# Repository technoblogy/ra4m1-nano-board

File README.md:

# RA4M1 Nano board
An Arduino Nano-sized board based on the Renesas RA4M1 ARM processor.

For more information see <http://www.technoblogy.com/show?4JVF>.

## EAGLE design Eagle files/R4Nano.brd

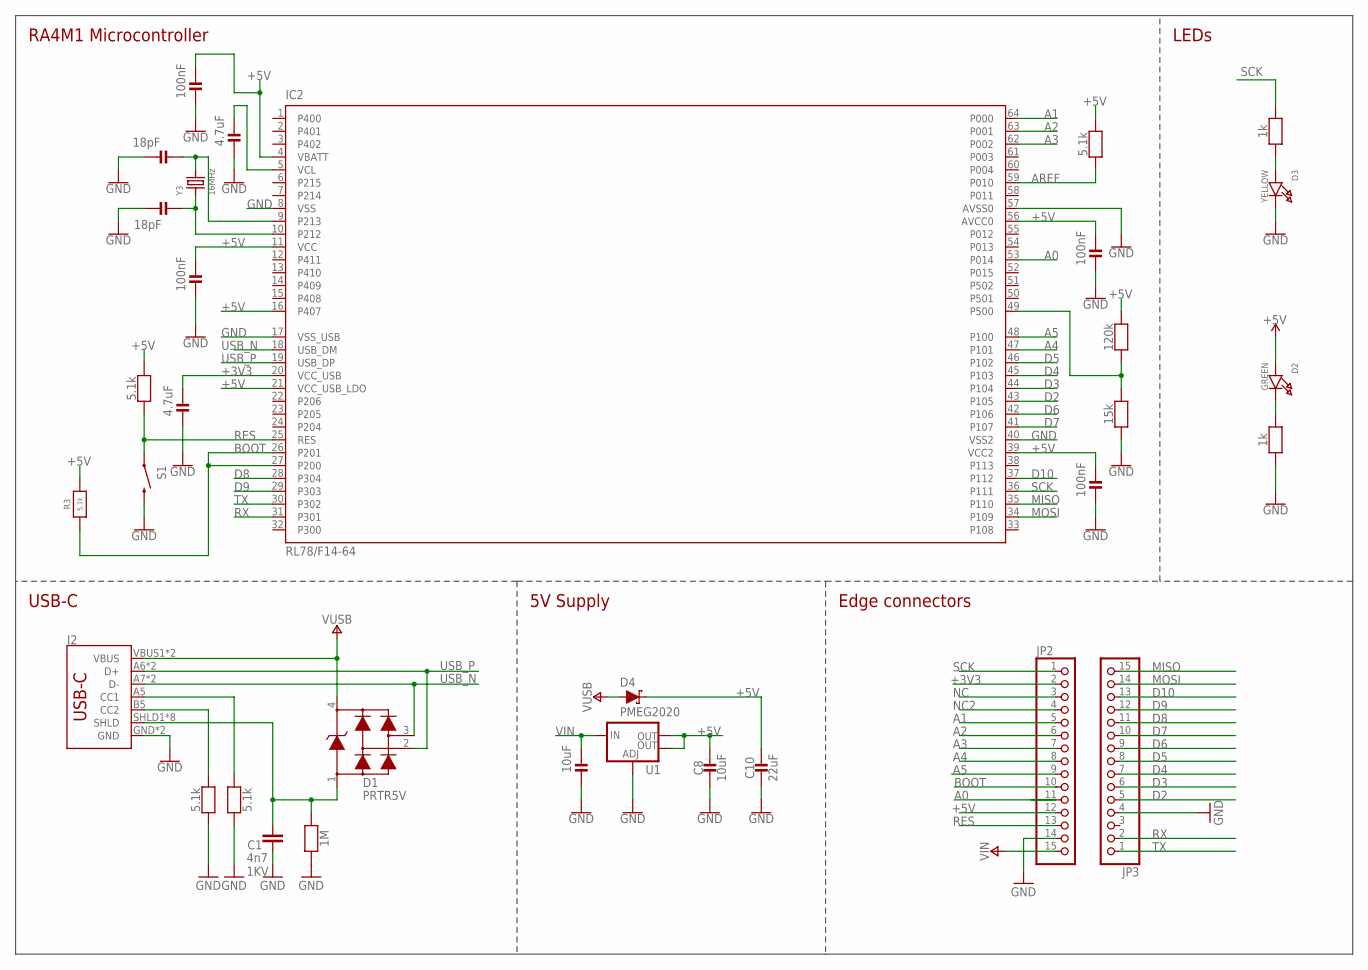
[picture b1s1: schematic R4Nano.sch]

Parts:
C1: 4n7; 0805-R2013X50N; VOLTAGE 1KV
C2, C5: 4.7uF; _0805MP
C3, C4, C6, C9: 100nF; _0805MP
C7, C8: 10uF; _0805MP
C10: 22uF; _0805MP
C12, C13: 18pF; _0805MP
D1: PRTR5V; SOT190P230X110-4N
D2: GREEN; CHIPLED_0805_NOOUTLINE
D3: YELLOW; CHIPLED_0805_NOOUTLINE
D4: PMEG2020; SOD-323
IC2: RL78/F14-64; P-LFQFP64-10X10
J2: USB_C2-LAYER; USB-C-16P
JP2, JP3: HEADER-1X15; 1X15_ROUND_70
R1: 1M; _0805MP
R2, R3, R4, R6, R8: 5.1k; _0805MP
R5, R12: 1k; _0805MP
R10: 120k; _0805MP
R11: 15k; _0805MP
S1: SWITCH-MOMENTARY-2SMD-4.6X2.8MM; TACTILE_SWITCH_SMD_4.6X2.8MM
U1: V_REG_LM1117SOT223; SOT223
Y3: 16MHz; CRYSTAL_2.5X2

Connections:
+3V3: C5.1, IC2.20 (VCC_USB), JP2.2
+5V: C3.1, C4.1, C6.1, C8.1, C9.1, C10.1, D2.A, D4.C, IC2.4 (VBATT), IC2.11 (VCC), IC2.16 (P407), IC2.21 (VCC_USB_LDO), IC2.39 (VCC2), IC2.56 (AVCC0), JP2.12, R2.1, R3.1, R4.1, R10.1, U1.2 (OUT), U1.4 (OUT)
A0: IC2.53 (P014), JP2.11
A1: IC2.64 (P000), JP2.5
A2: IC2.63 (P001), JP2.6
A3: IC2.62 (P002), JP2.7
A4: IC2.47 (P101), JP2.8
A5: IC2.48 (P100), JP2.9
AREF: IC2.59 (P010), R2.2
BOOT: IC2.26 (P201), IC2.27 (P200), JP2.10, R3.2
CC1: J2.A5 (CC1), R8.1
CC2: J2.B5 (CC2), R6.1
D2: IC2.43 (P105), JP3.5
D3: IC2.44 (P104), JP3.6
D4: IC2.45 (P103), JP3.7
D5: IC2.46 (P102), JP3.8
D6: IC2.42 (P106), JP3.9
D7: IC2.41 (P107), JP3.10
D8: IC2.28 (P304), JP3.11
D9: IC2.29 (P303), JP3.12
D10: IC2.37 (P112), JP3.13
GND: C1.2, C2.2, C3.2, C4.2, C5.2, C6.2, C7.2, C8.2, C9.2, C10.2, C12.2, C13.2, D3.C, IC2.8 (VSS), IC2.17 (VSS_USB), IC2.40 (VSS2), IC2.57 (AVSS0), J2.GND, J2.GND2 (GND), JP2.14, JP3.4, R1.2, R5.1, R6.2, R8.2, R11.2, S1.3 (2), S1.4 (2), U1.1 (ADJ)
MISO: IC2.35 (P110), JP3.15
MOSI: IC2.34 (P109), JP3.14
unnamed: C12.1, IC2.9 (P213), Y3.3 (2)
unnamed: C13.1, IC2.10 (P212), Y3.1
unnamed: C2.1, IC2.5 (VCL)
unnamed: D2.C, R5.2
unnamed: D3.A, R12.2
unnamed: IC2.49 (P500), R10.2, R11.1
NC: JP2.3
NC2: JP2.4
RES: IC2.25 (RES), JP2.13, R4.2, S1.1, S1.2 (1)
RX: IC2.31 (P301), JP3.2
SCK: IC2.36 (P111), JP2.1, R12.1
SHIELD: C1.1, D1.1, J2.SHLD1 (SHLD), J2.SHLD2 (SHLD), J2.SHLD3 (SHLD), J2.SHLD4 (SHLD), J2.SHLD5 (SHLD), J2.SHLD6 (SHLD), J2.SHLD7 (SHLD), J2.SHLD8 (SHLD), R1.1
TX: IC2.30 (P302), JP3.1
USB_N: D1.3, IC2.18 (USB_DM), J2.A7 (D-), J2.B7 (D-)
USB_P: D1.2, IC2.19 (USB_DP), J2.A6 (D+), J2.B6 (D+)
VIN: C7.1, JP2.15, U1.3 (IN)
VUSB: D1.4, D4.A, J2.VBUS1 (VBUS), J2.VBUS2 (VBUS)

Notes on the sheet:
USB-C
RA4M1 Microcontroller
LEDs
5V Supply
Edge connectors

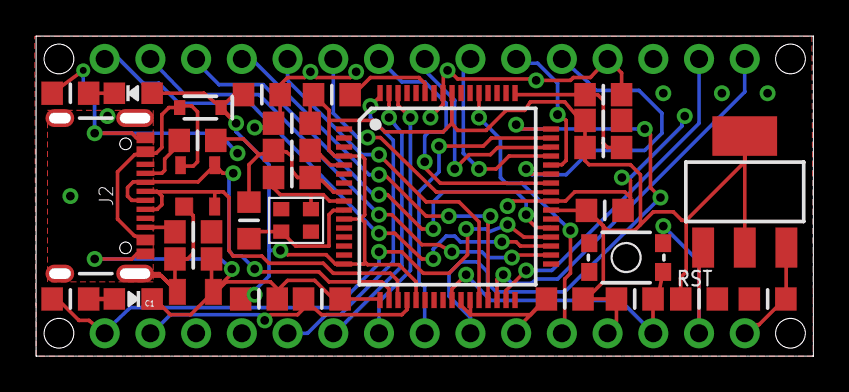
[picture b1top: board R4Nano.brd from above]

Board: 2 copper layers, 42.6 x 17.2 mm, 33 parts (0 on the bottom side), 39 nets.

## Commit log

2024-01-16 Version 1 - 16th January 2024

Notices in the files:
Eagle files/R4Nano.brd:
Copyright (c) 2016-2017 Arduino LLC.  All right reserved. EAGLE Design Rules
parts and their libraries:
technoblogy: Licensing: Creative Commons ShareAlike 4.0 International - https://creativecommons.org/licenses/by-sa/4.0
microbuilder: This work is placed in the public domain, and may be freely used for commercial and non-commercial work with the following conditions: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
